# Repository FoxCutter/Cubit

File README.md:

# Cubit
Source code repo for the Cubit z80 computer project

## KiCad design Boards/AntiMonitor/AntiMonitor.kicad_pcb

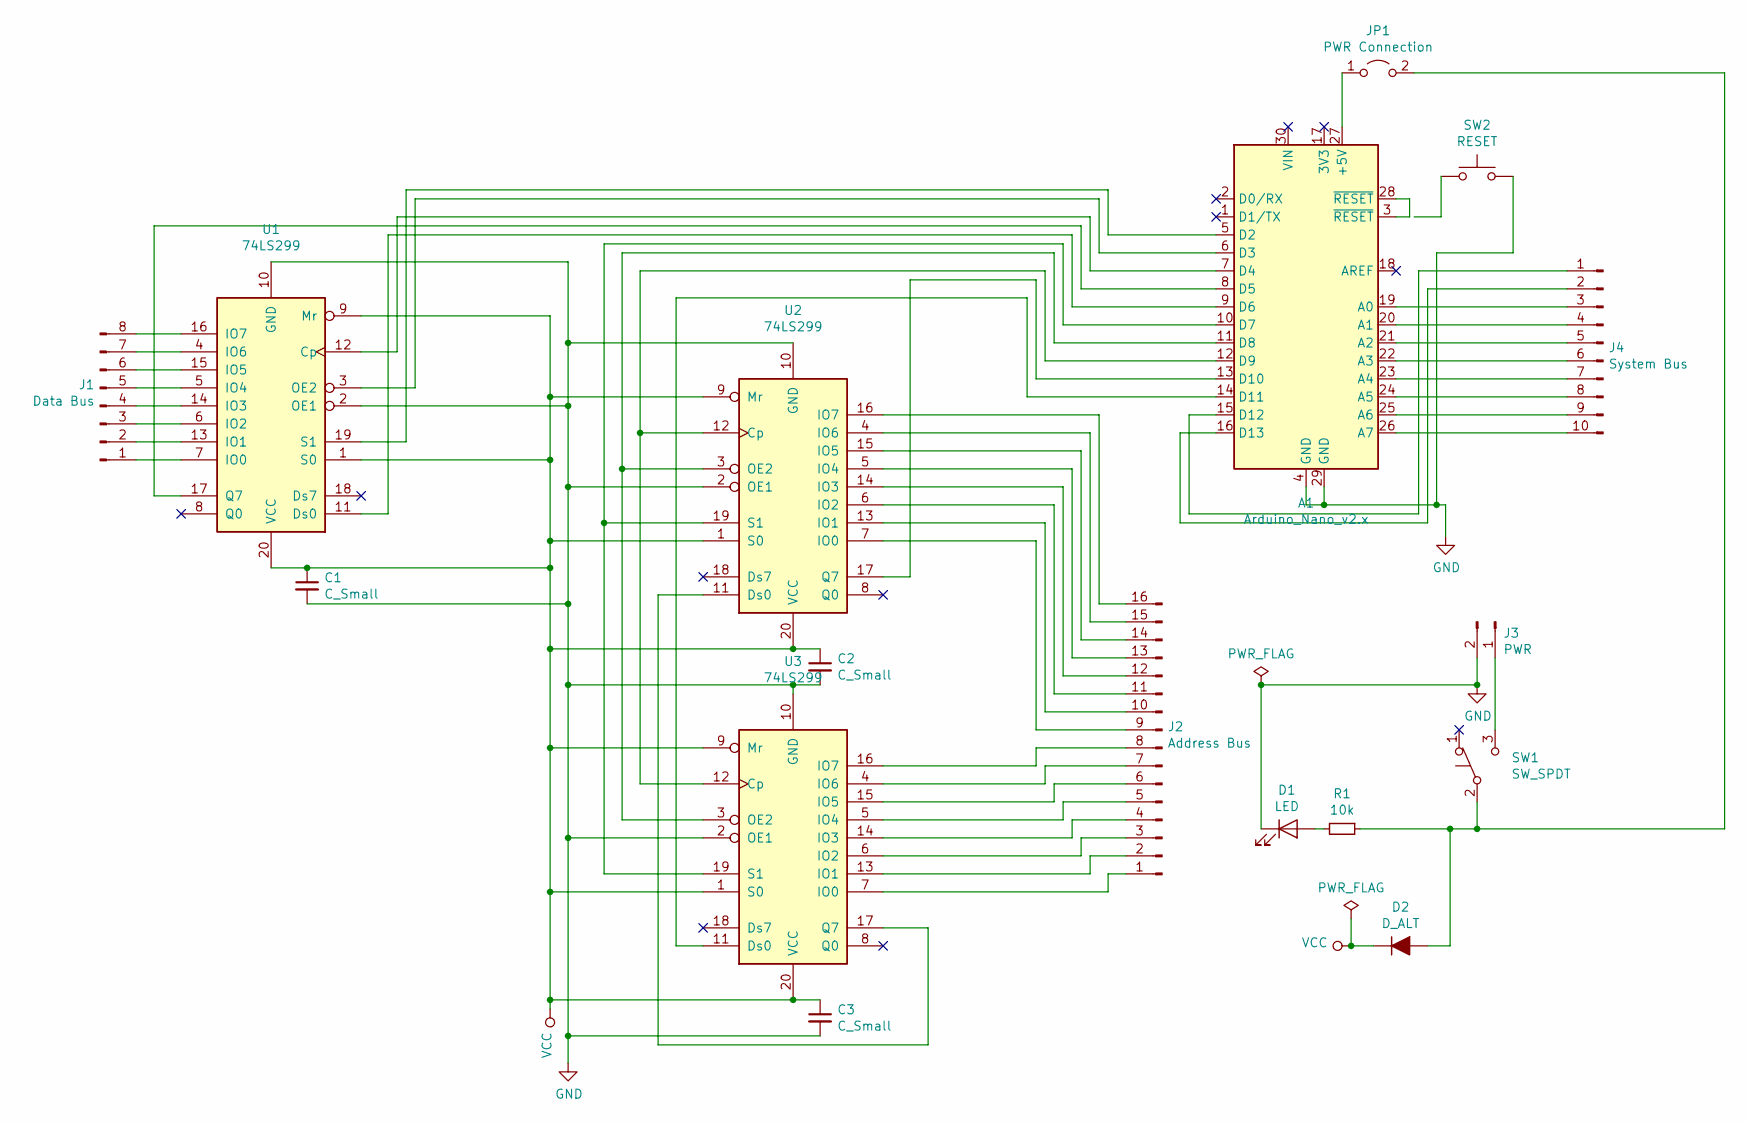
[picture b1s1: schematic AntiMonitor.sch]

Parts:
A1: Arduino_Nano_v2.x; Arduino_Nano
C1, C2, C3: C_Small; C_Disc_D3.0mm_W1.6mm_P2.50mm
D1: LED; LED_D3.0mm
D2: D_ALT; D_A-405_P7.62mm_Horizontal
J1: Data Bus; PinHeader_1x08_P2.54mm_Vertical
J2: Address Bus; PinHeader_1x16_P2.54mm_Vertical
J3: PWR; PinHeader_1x02_P2.54mm_Vertical
J4: System Bus; PinHeader_1x10_P2.54mm_Vertical
JP1: PWR Connection; PinHeader_1x02_P2.54mm_Vertical
R1: 10k; R_Axial_DIN0207_L6.3mm_D2.5mm_P7.62mm_Horizontal
SW1: SW_SPDT; SW_CuK_JS202011CQN_DPDT_Straight
SW2: RESET; SW_PUSH_6mm_H5mm
U1, U2, U3: 74LS299; DIP-20_W7.62mm_Socket

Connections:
GND: A1.4 (GND), A1.29 (GND), C1.2, C2.2, C3.2, D1.1 (K), J3.2, SW2.2, U1.2 (OE1), U1.10 (GND), U2.2 (OE1), U2.10 (GND), U3.2 (OE1), U3.10 (GND)
unnamed: A1.5 (D2), U1.19 (S1)
unnamed: A1.6 (D3), U1.3 (OE2)
unnamed: A1.7 (D4), U1.12 (Cp)
unnamed: A1.8 (D5), U1.17 (Q7)
unnamed: A1.9 (D6), U1.11 (Ds0)
unnamed: A1.10 (D7), U2.19 (S1), U3.19 (S1)
unnamed: A1.11 (D8), U2.3 (OE2), U3.3 (OE2)
unnamed: A1.12 (D9), U2.12 (Cp), U3.12 (Cp)
unnamed: A1.13 (D10), U2.17 (Q7)
unnamed: A1.14 (D11), U3.11 (Ds0)
unnamed: A1.15 (D12), J4.1
unnamed: A1.16 (D13), J4.2
unnamed: A1.19 (A0), J4.3
unnamed: A1.20 (A1), J4.4
unnamed: A1.21 (A2), J4.5
unnamed: A1.22 (A3), J4.6
unnamed: A1.23 (A4), J4.7
unnamed: A1.24 (A5), J4.8
unnamed: A1.25 (A6), J4.9
unnamed: A1.26 (A7), J4.10
unnamed: A1.27 (+5V), JP1.1 (A)
unnamed: A1.3 (~RESET), A1.28 (~RESET)
unnamed: D1.2 (A), R1.2
unnamed: D2.2 (A), JP1.2 (B), R1.1, SW1.2 (B)
unnamed: J1.1, U1.7 (IO0)
unnamed: J1.2, U1.13 (IO1)
unnamed: J1.3, U1.6 (IO2)
unnamed: J1.4, U1.14 (IO3)
unnamed: J1.5, U1.5 (IO4)
unnamed: J1.6, U1.15 (IO5)
unnamed: J1.7, U1.4 (IO6)
unnamed: J1.8, U1.16 (IO7)
unnamed: J2.1, U3.7 (IO0)
unnamed: J2.2, U3.13 (IO1)
unnamed: J2.3, U3.6 (IO2)
unnamed: J2.4, U3.14 (IO3)
unnamed: J2.5, U3.5 (IO4)
unnamed: J2.6, U3.15 (IO5)
unnamed: J2.7, U3.4 (IO6)
unnamed: J2.8, U3.16 (IO7)
unnamed: J2.9, U2.7 (IO0)
unnamed: J2.10, U2.13 (IO1)
unnamed: J2.11, U2.6 (IO2)
unnamed: J2.12, U2.14 (IO3)
unnamed: J2.13, U2.5 (IO4)
unnamed: J2.14, U2.15 (IO5)
unnamed: J2.15, U2.4 (IO6)
unnamed: J2.16, U2.16 (IO7)
unnamed: J3.1, SW1.3 (C)
unnamed: U2.11 (Ds0), U3.17 (Q7)
VCC: C1.1, C2.1, C3.1, D2.1 (K), U1.1 (S0), U1.9 (Mr), U1.20 (VCC), U2.1 (S0), U2.9 (Mr), U2.20 (VCC), U3.1 (S0), U3.9 (Mr), U3.20 (VCC)

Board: 2 copper layers, 17 parts (0 on the bottom side), 52 nets, no tracks yet.

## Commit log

2016-05-24 Added Interrupt Controller.
2016-05-24 Added the Anti-Monitor code.
2016-05-24 z80 monitor code.
2016-05-24 Board design file
2016-05-24 * Adding Tools
2016-05-27 * Adding keywords and IDs to the tokenizer * very basic name table support
2016-06-01 Minor Tokenizer Tweeks
2016-06-01 Updated file
2016-06-01 * More Tokenizer Improvements * Early RPN stack for parameters * very basic local labels
2016-06-02 * Building out a full Parser * Operator Precedent done (and maybe even right!) * Full set up operation tokens
2016-06-03 * Improved Table Builder * Can now resolve first pass values * Support for Hex, Dec, Oct and Bin number types * Better label detection *
2016-06-07 * Tokenizer updates
2016-06-07 * Reworking the Parser
2016-06-09 * Large update to the opcode tables * Added a flag for opcodes that can assume the A register will be used (IE, SUB C will be treated as SUB A, C) * Everything with an assumed A now has the register 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
2016-06-09 * Added Types to the Params * Can look up most opcodes based on Types and known registers * Some work around for a few oddly formatted 'official' opcodes (like IN (C) ) * More to come...
2016-06-10 * Minor Tweak to the table builder
2016-06-10 * Improved error logging, less exceptions more actual log
2016-06-10 * Improved the Tokenizer a bit more * Error output * The symbol table know keeps refs instead of lines * Some error checking now * Re-did the opcode table matching again, it's MUCH better now. * Star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
2016-06-15 * Reworked the parser to be more object based * Removed passing around tokens in many places (still have a lot of them around though). * Location information moved into a standalone object so it can 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
2016-06-16 * Broke the Parameter code into their own class and simplified a few things
2016-06-17 * Removing the value from the symbol tables, and other general cleanup.
2016-06-17 * Changed how the opcode tables are made for ZASM * Calculated opcode Length * Improvements in looking up Opcodes
2016-06-24 * Support for three parameter opcodes * Cleaned up the opcode tables * More error checking * Correct address calculations
2016-06-24 * trying to add rules for values
2016-07-08 * Extra opcode info for ZASM encoding
2016-07-13 Added support for $ to be 'current pos' and a hex prefix.
2016-07-15 * Starting on a working version of the monitor code
2016-07-21 Bus Notes
2016-07-28 * Board file update
2016-08-12 Board and bus updates
2016-09-23 * General rewrite of the parsing system, should be easier to extend.
2016-10-07 * Returned the location information into tokens, to useful to dump * Rewrote the list of .commands and pusdo opcodes to be more in line with what I want it to be.
2016-12-02 Removed the otherwise useless FileInformation object
2016-12-02 Removed the Token Location object, shouldn't be used in that context.
2016-12-02 Removed uncommon items from the ObjectInformation and tightened things up a bit.
2016-12-16 Added some Meta tracking objects
2016-12-16 Working on new opcodes data format
2017-08-17 * Better opcode table building and formatting
2017-09-13 A mess of changes
2017-09-15 MU branch
2017-09-21 * More updates to ZASM Mu
2017-09-22 More rewriting of ZASM
2017-09-26 * Continuing the rewrite, basic param parsing.
2017-09-28 * Parameter parsing and execution added. All around error handling for bad constructs and some other clean up.
2017-09-29 * Minor parsing updates
2017-10-05 * Opcode Matrix Updates
2017-10-05 * Adding table builder and opcode data
2017-10-06 * More tweaks in the opcode generation
2017-10-06 * General improvements to some parsing rules after testing real code * Opcode looks are now working. * Stage one is effectively completed.
2017-10-09 * Address finally being set, current position working and readjusted equ to be a fixed constant.
2017-10-20 * Minor fixes and tweaks to the table builder for emulation data.
2017-10-20 * Added a 4-bit Hex to 7 segment decoder * Minor fixes to the Interrupt Controller
2017-10-20 * Renamed folder
2017-10-20 * Pin corrections * Updated readme.
2017-10-20 * Test timing improvments.
2017-10-27 * Reworking interrupt controller.
2018-05-19 * 8th or 9th Table builder rewrite, this one might even stick * Moved all the opcode defines from the XLSX/Text file mess to a single XML file, with schema * Unified a number of the different objects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
2018-05-21 * New Working Branch
2018-05-23 * Rebuilding ZASM with some new designs
2018-06-01 * Table builder now outputs a map of Mnemonics to CommandIDs. * Parameter list data tables for all three platforms (should be from table builder as well) * Settings Object with basic defaults and the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
2018-06-06 * Very early parser support for commands * Can switch Opcodes * Support for Include files * Support for Listing File
2018-06-07 * Conditional compiling (without evaluation) added * Symbol Table added * Parser split into 3 files for each phase
2018-06-08 * Basic Opcode parsing * Basic Parameter Parsing * Handle labels without : * Basic value handling * Cycle Count in listing file * Fixed values shown in listing file
2018-06-12 * Unified common code elements in the parser * Basic value parsing
2018-06-13 * Minor T week to the Gameboy encoding rules to correct support (c) and (n) for high memory access.
2018-06-14 * More Parameter parsing. * Tweeked the error Messages * Added Assumed A logic, Index off, CY as Carry and the basics for @ as address of (if that's on you labels can't start with @) * Added support 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
2018-12-05 Tweaking the segment code
2019-01-27 Antimonitor tweaks
2019-08-29 A number of changes to the XML opcode data * Encoding Enum values have been renamed to be useful, added 'direct' for arguments that are a fix part of the opcode * Encoding is now required on all argu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
2019-09-06 * More opcode encoding improvements * Flag data added to the Opcode XML file
2020-02-24 Adding KiCad files for a PCB AntiMonitor board
2020-02-25 Removing the old Tools folder
2020-10-10 * Code Cleanup * Debug Output * Renamed a few things to be more clear * Support :: for public labels
2020-12-15 One more table builder improvement
2022-08-26 * Antimonitor board update * INT controller tweaks * Opcode XML adjusted slightly * Table builder to output C++ EMU tables * ZASM updates
2022-08-26 Added Fourth Kernel
2022-08-26 * Redoing the timings in the opcode tables * Fixing a couple generation issues in both the xml and table builder
2022-08-26 * More opcode tweaks
